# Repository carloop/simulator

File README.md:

# CAN Simulator

This is a project we used to help develop and test the [Carloop open-source car adapter][carloop]. We hope you'll find it useful for your projects too.

## Overview

The simulator consists of:
- An OBD port (the same you have in your car under the steering wheel) to plug a device to test
- The simulator board to convert CAN voltages to logic levels and provide 12V on the OBD port
- A Raspberry Pi to run the simulator program
- [The program][simulator-program] that communicates with the simulator board and that decide what to do with the CAN messages received

## Background about CAN

CAN is the communication bus used between most computers in cars. It has several physical layers, including a high-speed differential voltage (CAN high and CAN low) at up to 1 Mbit/second. CAN is a multicast protocol where each message has an identifier and up to 8 data bytes. Any node listening on the bus can receive any message transmitted. In order to make sense of the messages, the receivers need to know the data format used by the transmitter of each message for the data bytes.

There are higher level protocols built on top of CAN, most importantly ISO 15765 used for OBD-II (On-Board Diagsnotics II) mandated on all cars since 2008 and used on many cars before. See [this tutorial by Sparkfun for more information about the OBD-II protocol][obd-getting-started]

This CAN simulator can be used to transmit and receive messages simulating OBD-II communications and regular vehicle messages.

## Simulator board

The heart of the simulator board is the [MCP2515 standalone CAN controller][mcp2515-datasheet] that understands the CAN protocol
and talks to the Raspberry Pi over the SPI bus.

The board also has a [TJA1049 CAN transceiver][tja1049-datasheet] to translate logic voltage levels to the differential voltage levels used for high speed CAN.

Since the OBD port is supposed to provide 12 volts, a simple [5V to 12V step up regulator from Pololu][12v-step-up-regulator] is included.

The OBD connector is part of an off-the-shelf [9-pin OBD ribbon extension cable available on Amazon][obd-cable].

- [Board schematics (PDF)][schematics] [(Eagle)][schematics-eagle]
- [Board layout (Eagle)][layout-eagle]
- [Bill of materials][bom]
- [MCP2515 CAN controller datasheet][mcp2515-datasheet]
- [TJA1049 CAN transceiver datasheet][tja1049-datasheet]

### Assembly instructions

- [Order a simulator v1 PCB from OSH Park.][pcb-osh-park]
- [Order the parts from the BOM from DigiKey][bom] and the [regulator from Pololu.][12v-step-up-regulator]
- Solder the above together.
- Get a Raspberry Pi with a GPIO connector.
- [Get an OBD cable.][obd-cable]
- Insert the 9-pin flat cable in the 10-pin insulation displacement connector aligned to the left (see the overview picture above) and cut the leftover cable.
- Flash the latest Raspian image to the SD card of your Raspberry PI and follow the instructions to get the simulator program running.

## [Simulator program][simulator-program]

The program running the simulation is in [a separate repository][simulator-program]. Currently it only sends fixed messages. It could be extended for more sophisticated communication or to replay logged CAN bus traces.

## License

Copyright 2016 Julien Vanier. Distributed under the MIT license. See [LICENSE](/LICENSE) for details.

[carloop]: https://www.carloop.io
[simulator-program]: https://github.com/carloop/simulator-program
[schematics]: eagle/CAN-Simulator_v1.1.pdf
[schematics-eagle]: eagle/CAN-Simulator_v1.1.sch
[layout-eagle]: eagle/CAN-Simulator_v1.1.brd
[bom]: eagle/CAN-Simulator_v1_BOM.csv
[obd-getting-started]: https://learn.sparkfun.com/tutorials/getting-started-with-obd-ii
[obd-cable]: https://www.amazon.com/gp/product/B00GGLVXG2/ref=oh_aui_detailpage_o02_s00?ie=UTF8&psc=1
[mcp2515-datasheet]: datasheets/MCP2515%20Datasheet.pdf
[tja1049-datasheet]: datasheets/TJA1049%20Datasheet.pdf
[12v-step-up-regulator]: https://www.pololu.com/product/2117
[pcb-osh-park]:https://oshpark.com/shared_projects/GOPwocjS

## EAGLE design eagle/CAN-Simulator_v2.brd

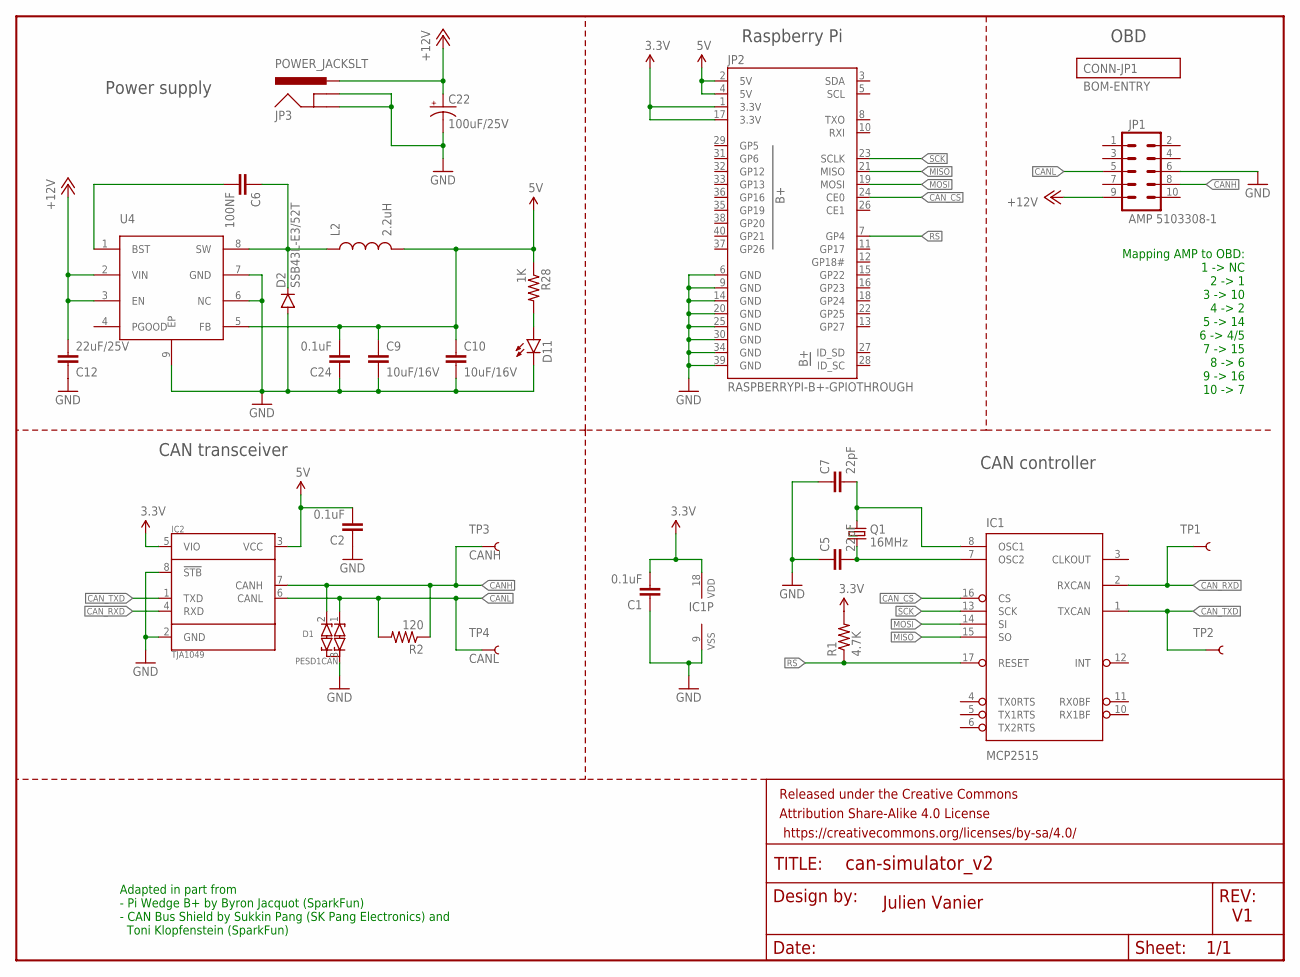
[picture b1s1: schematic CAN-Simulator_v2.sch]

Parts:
C1, C2, C24: 0.1uF; 0402-CAP
C5, C7: 22pF; C0805; PARTNO C0805C220J5GACTU
C6: 100NF; 0402-CAP
C9, C10: 10uF/16V; 0805-CAP
C12: 22uF/25V; 1210
C22: 100uF/25V; CPOL-RADIAL-100UF-25V
D1: PESD1CAN; SOT23; PARTNO PESD1CAN-215
D2: SSB43L-E3/52T; SMB-DIODE
D11: LED0603; LED-0603
FRAME1: FRAME-LETTER; CREATIVE_COMMONS
IC1: MCP2515; SO-18W; PARTNO MCP2515-I/SO
IC2: TJA1049; SO8; PARTNO TJA1049T-118
JP1: AMP 5103308-1; 2X5-SHROUDED; PARTNO 5103308-1
JP2: RASPBERRYPI-B+-GPIOTHROUGH; PIN_20X2
JP3: POWER_JACKSLT; POWER_JACK_SLOT
L2: 2.2uH; I4818
Q1: 16MHz; CRYSTAL-SMD-5X3; PARTNO ABM3B-16.000MHZ-10-1-U-T
R1: 4.7K; R0402; PARTNO RC0805JR-0747KL
R2: 120; R0603; PARTNO RC0603FR-07120RL
R28: 1K; 0402-RES
TP1, TP2: TEST-POINT3X5; PAD.03X.05
TP3: CANH; PAD.03X.03
TP4: CANL; PAD.03X.03
U4: ADP2303; ADP2302

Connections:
3.3V: C1.2, IC1.18 (VDD), IC2.5 (VIO), JP2.1 (3.3V), JP2.17 (3.3V), R1.2
5V: C2.2, C9.1, C10.1, C24.2, IC2.3 (VCC), JP2.2 (5V), JP2.4 (5V), L2.2, R28.1, U4.5 (FB)
+12V: C12.2, C22.1 (+), JP1.9, JP3.PWR, U4.2 (VIN), U4.3 (EN)
CANH: D1.2 (C2), IC2.7 (CANH), JP1.8, R2.1, TP3.P$1
CANL: D1.1 (C1), IC2.6 (CANL), JP1.5, R2.2, TP4.P$1
CAN_CS: IC1.16 (CS), JP2.24 (CE0)
CAN_RXD: IC1.2 (RXCAN), IC2.4 (RXD), TP1.P$1
CAN_TXD: IC1.1 (TXCAN), IC2.1 (TXD), TP2.P$1
GND: C1.1, C2.1, C5.1, C7.1, C9.2, C10.2, C12.1, C22.2 (-), C24.1, D1.3 (COM), D2.A, D11.C, IC1.9 (VSS), IC2.2 (GND), IC2.8 (!STB), JP1.6, JP2.6 (GND), JP2.9 (GND), JP2.14 (GND), JP2.20 (GND), JP2.25 (GND), JP2.30 (GND), JP2.34 (GND), JP2.39 (GND), JP3.GND@1 (GNDBREAK), JP3.GND@2 (GND), U4.6 (NC), U4.7 (GND), U4.9 (EP)
MISO: IC1.15 (SO), JP2.21 (MISO)
MOSI: IC1.14 (SI), JP2.19 (MOSI)
unnamed: C7.2, IC1.8 (OSC1), Q1.3 (2)
unnamed: C5.2, IC1.7 (OSC2), Q1.1
unnamed: C6.2, U4.1 (BST)
unnamed: C6.1, D2.C, L2.1, U4.8 (SW)
unnamed: D11.A, R28.2
RS: IC1.17 (RESET), JP2.7 (GP4), R1.1
SCK: IC1.13 (SCK), JP2.23 (SCLK)

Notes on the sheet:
Julien Vanier
Adapted in part from - Pi Wedge B+ by Byron Jacquot (SparkFun) - CAN Bus Shield by Sukkin Pang (SK Pang Electronics) and Toni Klopfenstein (SparkFun)
Mapping AMP to OBD: 1 -> NC 2 -> 1 3 -> 10 4 -> 2 5 -> 14 6 -> 4/5 7 -> 15 8 -> 6 9 -> 16 10 -> 7
Raspberry Pi
OBD
CAN transceiver
CAN controller
Power supply

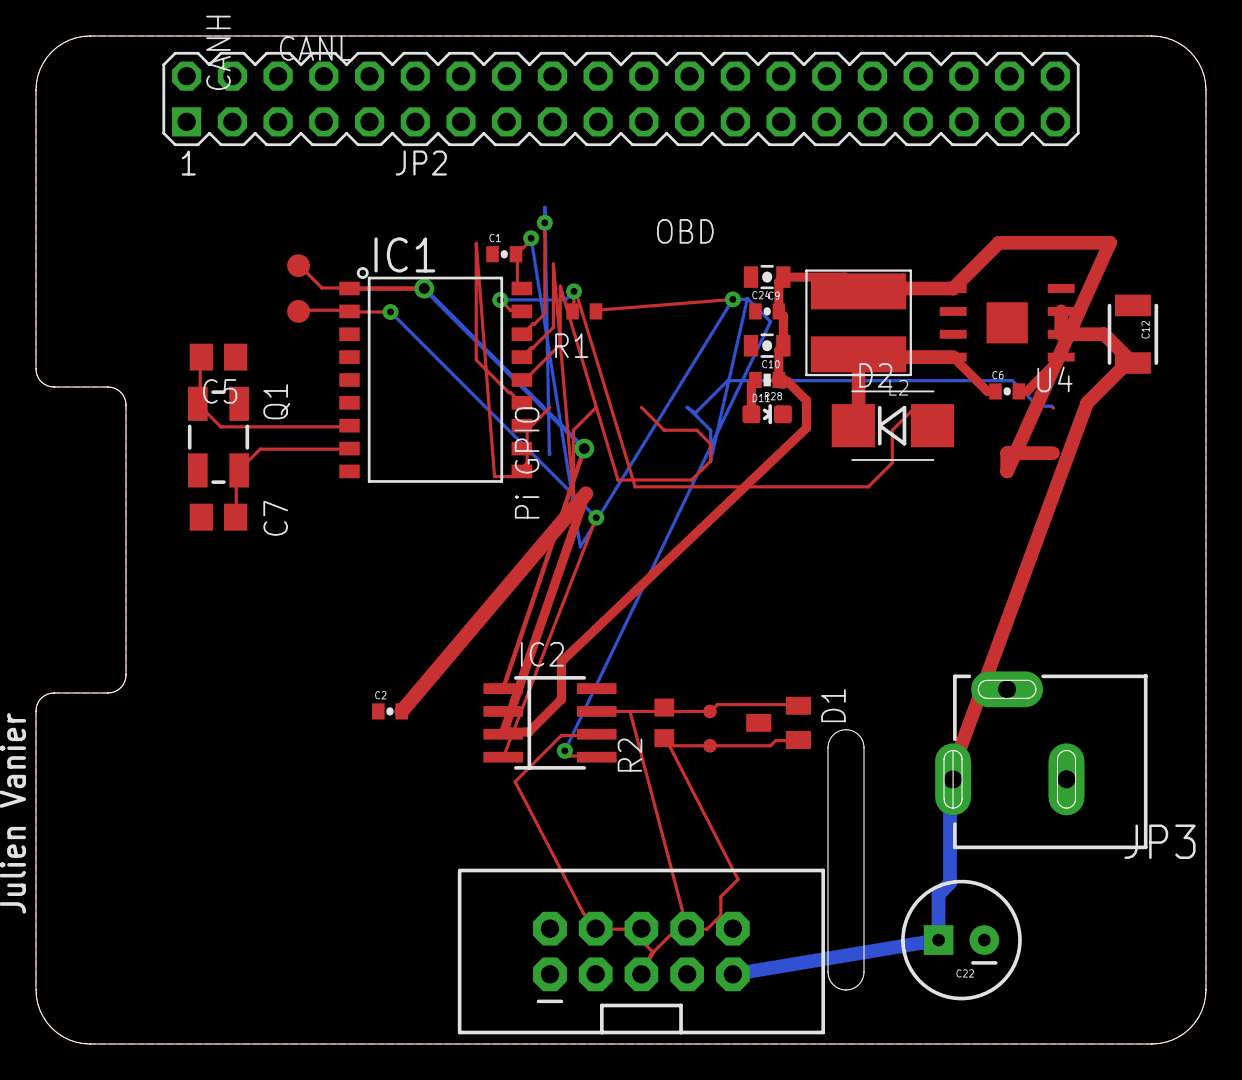
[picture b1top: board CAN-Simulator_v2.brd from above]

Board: 2 copper layers, 65.0 x 56.0 mm, 29 parts (0 on the bottom side), 18 nets.

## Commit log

2016-06-02 Simulator v1 working
2016-06-02 Update order of sections
2016-06-02 Add assembly instructions
2016-06-07 Fix borken link
2016-08-29 fixed CSV format
2018-01-30 Work in progress for CAN simulator V2
2018-06-03 Update PCB to 1.1 to distinguish board with corrected transceiver pin 8 ground
2018-06-03 Update README with v1.1 links

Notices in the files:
parts and their libraries:
SparkFun-Aesthetics: Licensing: CC v3.0 Share-Alike You are welcome to use this library for commercial purposes.
SparkFun-Aesthetics: Released under the Creative Commons Attribution Share-Alike 4.0 License
SparkFun-Aesthetics: https://creativecommons.org/licenses/by-sa/4.0
